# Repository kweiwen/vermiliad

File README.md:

# Vermiliad - An open-source hardware solution for building digital modular synthesizers
* DSP, Pure Data, and Controlled Voltage in a single pcb!
* 數位訊號處理、Pure Data、控制電壓融合在在一塊小小的PCB！

## DEMO1:
* 第一段影片展示了Talk-Through功能。首先使用 `aplay -l` 命令確認聲卡的輸入/輸出配置，隨後透過 `mplayer` 命令播放網絡電台。
* The first clip demonstrates the Talk-Through feature. It begins by using the `aplay -l` command to confirm the input/output configuration of the sound card, followed by playing an internet radio station using the `mplayer` command.
* 第二段影片展現了Pitch Shifting的Echo效果。該功能是透過Pure Data實現的，音源輸入來自於Benjolin。
* The second clip showcases the Echo effect of Pitch Shifting. This function is implemented through Pure Data, with the audio input sourced from Benjolin.
* 第三段影片的設置與第二段相同，但在效果器的參數上進行了調整。
* The setup in the third clip is the same as in the second, but with adjustments made to the parameters of the effects processor.
<video src="https://github-production-user-asset-6210df.s3.amazonaws.com/15021145/285418308-6633f0b2-d7b3-4ce2-ba0a-d69b2f7387a2.mp4" width="320" controls></video>

## DEMO2:
* 最後一段影片展示了基於Feedback Delay Network的Granular Delay，這同樣是透過Pure Data實現的，音源輸入來自於Benjolin。
* This final video demonstrates the Granular Delay based on Feedback Delay Networks, also implemented through Pure Data, with the audio input sourced from Benjolin.
<video src="https://github-production-user-asset-6210df.s3.amazonaws.com/15021145/285418398-cd53d4ac-97a0-486a-81fa-60b1c6fd6b72.mp4" width="320" controls></video>

## PCB Layout:

* Top Of Adapter

* Bottom Of Adapter

* Top Of Motherboard

* Bottom Of Motherboard

## Introduction:

This article introduces the master's thesis titled "Building an Open Source Modular Synthesizer Based on the Integration of Raspberry Pi, Python and Pure Data." initiated in late 2015. During my military service in Madou, Tainan, I continuously worked on and developed this project, efficiently adjusting and upgrading various hardware and software components. This module is designed for Real-Time DSP, allowing users to customize modular synthesizer functions on Pure Data. I also implemented Miller Puckette's Feedback Delay Network Reverb on Pure Data, receiving positive feedback. The project is ultimately managed as an open-source initiative, aiming to contribute more to the open-source community and synthesizer enthusiasts.

In terms of software, I found no better method than the UDP interface for transmitting data to Pure Data. I used MCP3008 to receive external control voltage parameters, then transmitted them to the UDP network via Python for Pure Data to read. However, Python's looped data transmission consumed significant memory. Even attempts using Linux Bash loops were unsatisfactory, as a 0.5-millisecond transmission frequency consumed 25% of the CPU and 18% of the memory. Python scripts were affected by Raspberry Pi and other unstable factors, leading to external control delays. Given that Python is an interpreted language, despite methods to improve performance, switching languages proved to be a better option.

Ultimately, I replaced Python with C++ as the interface for communication between MCP3008 and Raspberry Pi. This led to significant improvements: the sampling speed could reach 0.1 milliseconds or even faster, with about 3% memory usage and approximately 5% CPU occupancy. This change enhanced the operation's smoothness and provided more resources for processing audio inside Pure Data.

In hardware, I used the I2S audio transmission interface instead of the previous USB Audio, choosing the WM8731 chip, widely used by many module manufacturers. After upgrading the Linux kernel to 4.4, the I2S driver module was built into the kernel, relieving developers from the hassle of cross-compiling and significantly improving sound quality. The external control voltage circuit was designed with an OP Amp to adjust the voltage range to meet MCP3008's requirements. Major changes were made to the external output of the sound source, mixing the original signal with the Codec output, and using Vactrol to control the dry/wet signal ratio, replacing many DSP-type effects in digital loop control.

The board layout was divided into two parts: the Adapter responsible for Audio I/O and Analog I/O, and the Motherboard for expansion, such as adjusting the voltage to Eurorack Level, Vactrol Mixing, CV Adjustment, etc.

## Epilogue:

Regarding the development of Pure Data, it is regrettable that the main program is no longer updated. The interface and editor have hardly changed, and updates mainly focus on platform expansion, bug fixes, and adding specific libraries. With the stabilization of new platforms like Raspberry Pi, and BeagleBone and the improvement of various libraries and functions, the frequency of updates to the main program has gradually decreased. The new Deken Plugin will become an important tool for managing and adding libraries.

## License
Code: MIT license.

Hardware: cc-by-sa-3.0

By: Tseng Kweiwen

## 簡介:

本文介紹的碩士論文題目「基於Raspberry Pi、Python和Pure Data構建開源模組化合成器」始於2015年底。在服役於台南麻豆期間，我持續實作與開發，對許多硬體與軟體部分進行高效調整和升級。此模組是為了服務Real-Time DSP，允許使用者在Pure Data上自定義模組合成器功能。我還在Pure Data上實現了Miller Puckette的Feedback Delay Network的Reverb，獲得良好回饋。該項目最終以開源方式管理，旨在為開源社區和合成器愛好者貢獻更多。

在軟體方面，我未找到比UDP介面更合適的方法將數據傳輸到Pure Data。我使用MCP3008接收外部控制電壓參數，再通過Python傳輸至UDP網路供Pure Data讀取。然而，Python循環傳輸資料會大量消耗記憶體。即使嘗試過Linux Bash進行循環，結果仍不理想，0.5毫秒的傳輸頻率會消耗25%的CPU和18%的記憶體。Python腳本受Raspberry Pi和其他不穩定因素影響，導致外部控制延遲。鑑於Python是直譯式語言，儘管有提高效能的方法，更換語言仍是更佳選擇。

最終，我改用C++取代Python作為MCP3008與Raspberry Pi的通訊介面。這帶來顯著改善，取樣速度可達0.1毫秒甚至更快，記憶體使用率約3%，CPU佔用率約5%，使操作更加順暢，並為Pure Data提供更多資源。

在硬體方面，我採用I2S音訊傳輸介面取代舊有的USB Audio，選用WM8731晶片，該晶片已被許多模組製造商廣泛使用。Linux kernel升級至4.4後，驅動模組內建於kernel中，開發者無需煩惱cross-compiling，音質也顯著提升。外部控制電壓迴路設計了OP Amp迴路以調整電壓範圍，符合MCP3008的要求，並對音源外部輸出進行重大改動，原始訊號與Codec輸出訊號混合，使用Vactrol控制乾濕訊號比例，替代了許多DSP類型效果器在數位迴路中的控制。

板子布局被分為兩部分：Adapter負責Audio I/O和Analog I/O，Motherboard則用於擴充，例如調整電壓至Eurorack Level、Vactrol Mixing、CV Adjustment等。

## 後記：
在Pure Data的發展上，遺憾的是主程式已不再更新。操控模式介面幾無變化，更新主要針對平台擴充、臭蟲修復和新增特定Library等。隨著新型平台如Raspberry Pi、BeagleBone的穩定，以及多種Library和功能的完善，主程式的更新逐漸減少。新的Deken Plugin將成為管理和新增Library的重要工具。

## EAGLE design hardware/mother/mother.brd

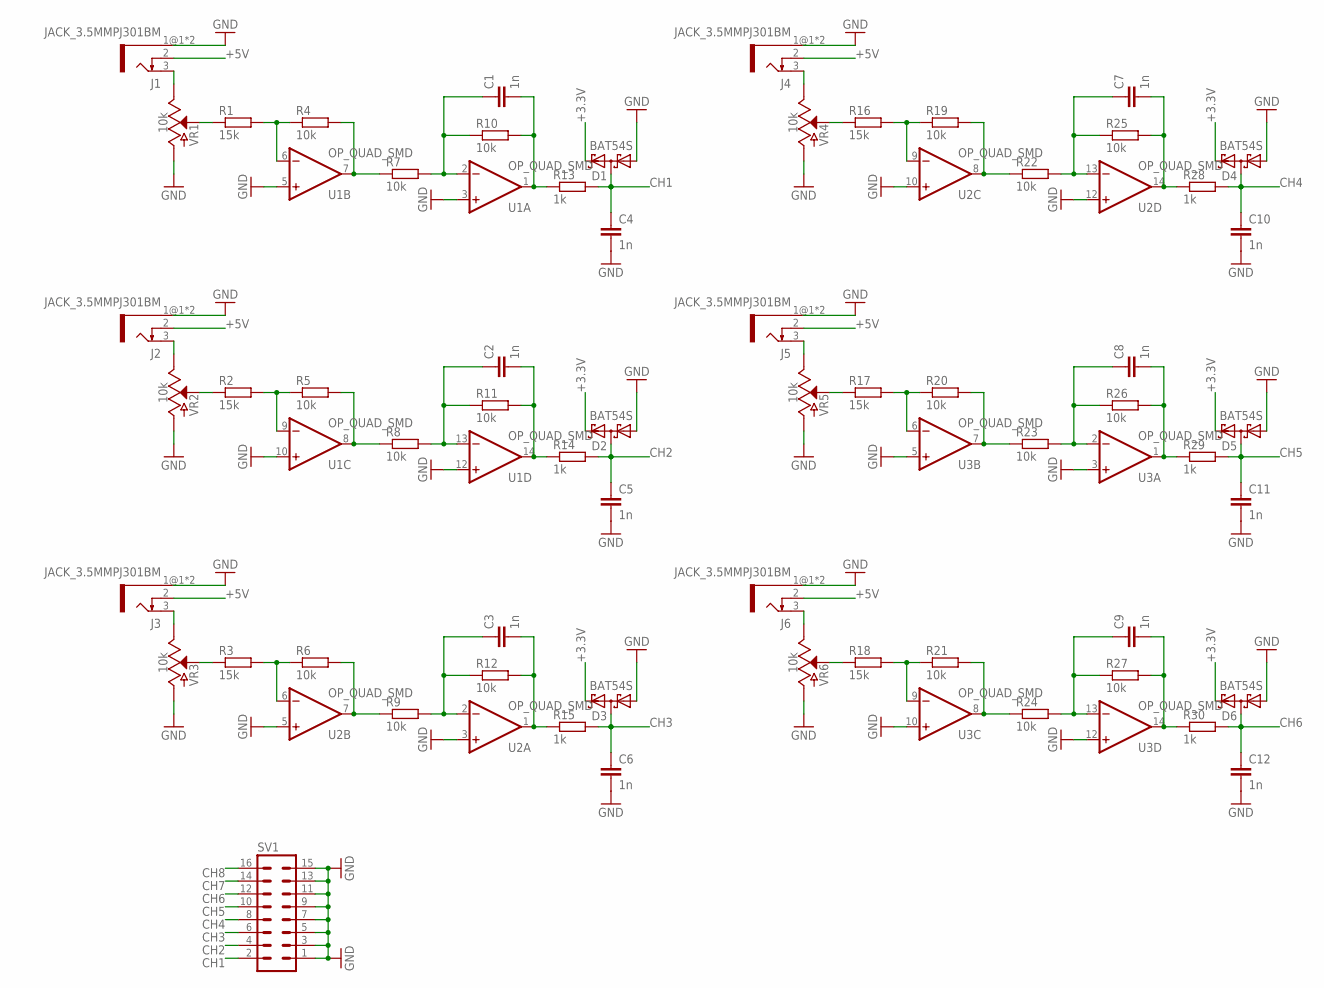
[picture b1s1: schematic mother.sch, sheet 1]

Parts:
C1, C2, C3, C4, C5, C6, C7, C8, C9, C10, C11, C12: 1n; C0603
D1, D2, D3, D4, D5, D6: BAT54S; SOT23
J1, J2, J3, J4, J5, J6: JACK_3.5MMPJ301BM; PJ301BM_JACK
R1, R2, R3, R16, R17, R18: 15k; R0603
R4, R5, R6, R7, R8, R9, R10, R11, R12, R19, R20, R21, R22, R23, R24, R25, R26, R27: 10k; R0603
R13, R14, R15, R28, R29, R30: 1k; R0603
SV1: MA08-2
U1, U2, U3: OP_QUAD_SMD; SO14
VR1, VR2, VR3, VR4, VR5, VR6: 10k; POT-PTH-ALPS-KIT

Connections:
+3.3V: D1.2 (C2), D2.2 (C2), D3.2 (C2), D4.2 (C2), D5.2 (C2), D6.2 (C2); also elsewhere on the board
+5V: J1.2, J2.2, J3.2, J4.2, J5.2, J6.2; also elsewhere on the board
CH1: C4.1, D1.3 (C1A2), R13.2, SV1.2
CH2: C5.1, D2.3 (C1A2), R14.2, SV1.4
CH3: C6.1, D3.3 (C1A2), R15.2, SV1.6
CH4: C10.1, D4.3 (C1A2), R28.2, SV1.8
CH5: C11.1, D5.3 (C1A2), R29.2, SV1.10
CH6: C12.1, D6.3 (C1A2), R30.2, SV1.12
CH7: SV1.14
CH8: SV1.16
GND: C4.2, C5.2, C6.2, C10.2, C11.2, C12.2, D1.1 (A1), D2.1 (A1), D3.1 (A1), D4.1 (A1), D5.1 (A1), D6.1 (A1), J1.1@1 (1), J1.1@2 (1), J2.1@1 (1), J2.1@2 (1), J3.1@1 (1), J3.1@2 (1), J4.1@1 (1), J4.1@2 (1), J5.1@1 (1), J5.1@2 (1), J6.1@1 (1), J6.1@2 (1), SV1.1, SV1.3, SV1.5, SV1.7, SV1.9, SV1.11, SV1.13, SV1.15, U1.3 (+IN), U1.5 (+IN), U1.10 (+IN), U1.12 (+IN), U2.3 (+IN), U2.5 (+IN), U2.10 (+IN), U2.12 (+IN), U3.3 (+IN), U3.5 (+IN), U3.10 (+IN), U3.12 (+IN), VR1.P$1 (A), VR2.P$1 (A), VR3.P$1 (A), VR4.P$1 (A), VR5.P$1 (A), VR6.P$1 (A); also elsewhere on the board
unnamed: R2.1, VR2.P$2 (S)
unnamed: J2.3, VR2.P$3 (E)
unnamed: R1.2, R4.1, U1.6 (-IN)
unnamed: R4.2, R7.1, U1.7 (OUT)
unnamed: C1.1, R7.2, R10.1, U1.2 (-IN)
unnamed: C1.2, R10.2, R13.1, U1.1 (OUT)
unnamed: R1.1, VR1.P$2 (S)
unnamed: R2.2, R5.1, U1.9 (-IN)
unnamed: R5.2, R8.1, U1.8 (OUT)
unnamed: J1.3, VR1.P$3 (E)
unnamed: C2.1, R8.2, R11.1, U1.13 (-IN)
unnamed: C2.2, R11.2, R14.1, U1.14 (OUT)
unnamed: R16.2, R19.1, U2.9 (-IN)
unnamed: R19.2, R22.1, U2.8 (OUT)
unnamed: C7.1, R22.2, R25.1, U2.13 (-IN)
unnamed: C7.2, R25.2, R28.1, U2.14 (OUT)
unnamed: R16.1, VR4.P$2 (S)
unnamed: J4.3, VR4.P$3 (E)
unnamed: R3.2, R6.1, U2.6 (-IN)
unnamed: R6.2, R9.1, U2.7 (OUT)
unnamed: C3.1, R9.2, R12.1, U2.2 (-IN)
unnamed: C3.2, R12.2, R15.1, U2.1 (OUT)
unnamed: R3.1, VR3.P$2 (S)
unnamed: J3.3, VR3.P$3 (E)
unnamed: R18.2, R21.1, U3.9 (-IN)
unnamed: R21.2, R24.1, U3.8 (OUT)
unnamed: C9.1, R24.2, R27.1, U3.13 (-IN)
unnamed: C9.2, R27.2, R30.1, U3.14 (OUT)
unnamed: R18.1, VR6.P$2 (S)
unnamed: J6.3, VR6.P$3 (E)
unnamed: R17.2, R20.1, U3.6 (-IN)
unnamed: R20.2, R23.1, U3.7 (OUT)
unnamed: C8.1, R23.2, R26.1, U3.2 (-IN)
unnamed: C8.2, R26.2, R29.1, U3.1 (OUT)
unnamed: R17.1, VR5.P$2 (S)
unnamed: J5.3, VR5.P$3 (E)

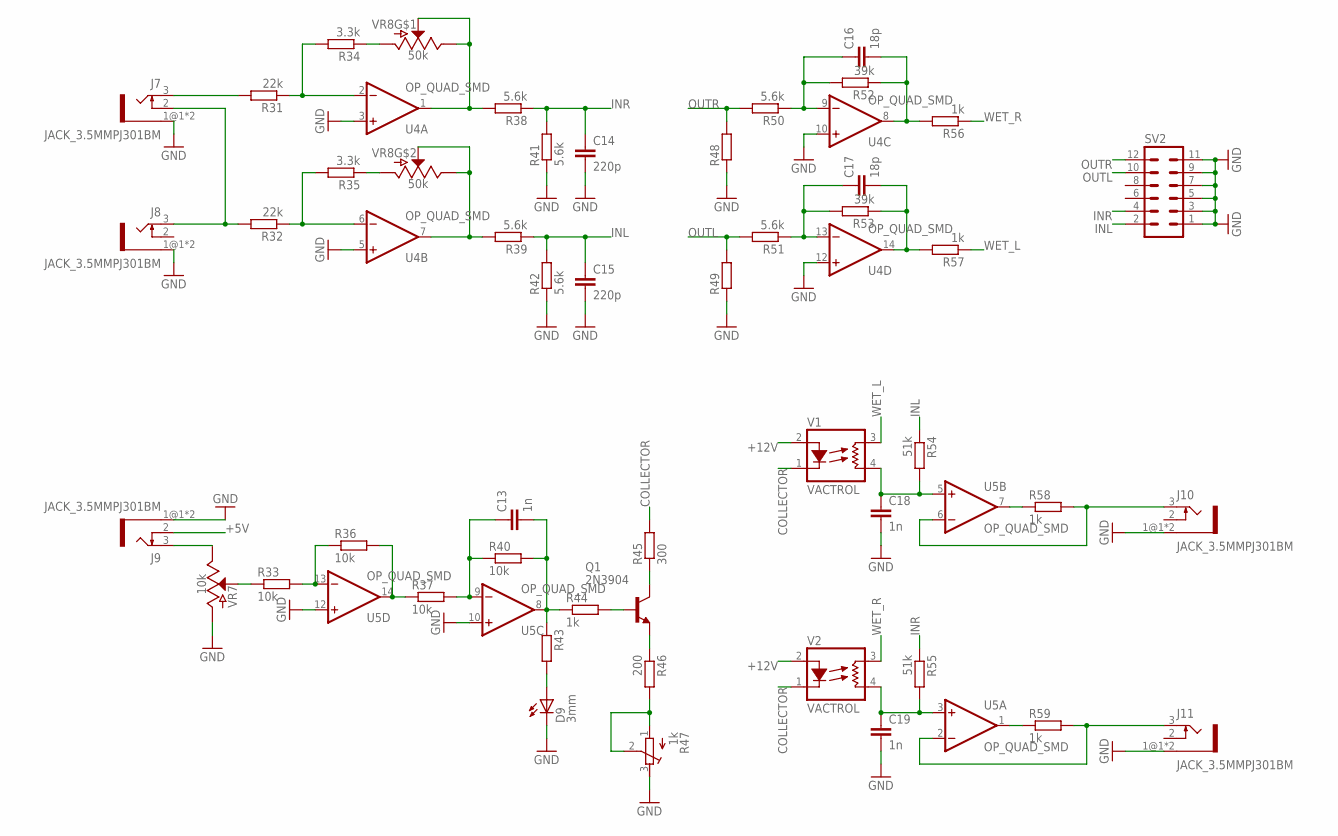
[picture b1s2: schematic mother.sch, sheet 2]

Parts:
C13, C18, C19: 1n; C0603
C14, C15: 220p; C0603
C16, C17: 18p; C0603
D9: 3mm; LED3MM
J7, J8, J9, J10, J11: JACK_3.5MMPJ301BM; PJ301BM_JACK
Q1: 2N3904; TO92
R31, R32: 22k; R0603
R33, R36, R37, R40: 10k; R0603
R34, R35: 3.3k; R0603
R38, R39, R41, R42, R50, R51: 5.6k; R0603
R43: RESISTOR10MM; 1/4W_RESISTOR
R44, R56, R57, R58, R59: 1k; R0603
R45: 300; 1/4W_RESISTOR
R46: 200; R0603
R47: 1k; RTRIM64W
R48, R49: RR0603; R0603
R52, R53: 39k; R0603
R54, R55: 51k; R0603
SV2: MA06-2
U4, U5: OP_QUAD_SMD; SO14
V1, V2: VACTROL; VACTROL_4PIN_VTL5C
VR7: 10k; POT-PTH-ALPS-KIT
VR8: 50k; POT-DUAL-PTH-PANASONIC-VERT-KIT

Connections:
+5V: J9.2; also elsewhere on the board
+12V: V1.2 (LED+), V2.2 (LED+); also elsewhere on the board
COLLECTOR: R45.2, V1.1 (LED-), V2.1 (LED-)
GND: C14.2, C15.2, C18.2, C19.2, D9.K (C), J7.1@1 (1), J7.1@2 (1), J8.1@1 (1), J8.1@2 (1), J9.1@1 (1), J9.1@2 (1), J10.1@1 (1), J10.1@2 (1), J11.1@1 (1), J11.1@2 (1), R41.1, R42.1, R47.3 (A), R48.1, R49.1, SV2.1, SV2.3, SV2.5, SV2.7, SV2.9, SV2.11, U4.3 (+IN), U4.5 (+IN), U4.10 (+IN), U4.12 (+IN), U5.10 (+IN), U5.12 (+IN), VR7.P$1 (A); also elsewhere on the board
INL: C15.1, R39.1, R42.2, R54.1, SV2.2
INR: C14.1, R38.1, R41.2, R55.1, SV2.4
unnamed: J9.3, VR7.P$3 (E)
unnamed: C13.2, R40.2, R43.1, R44.1, U5.8 (OUT)
unnamed: R33.1, VR7.P$2 (S)
unnamed: R33.2, R36.1, U5.13 (-IN)
unnamed: R36.2, R37.1, U5.14 (OUT)
unnamed: C13.1, R37.2, R40.1, U5.9 (-IN)
unnamed: D9.A, R43.2
unnamed: J10.3, R58.2, U5.6 (-IN)
unnamed: R58.1, U5.7 (OUT)
unnamed: C18.1, R54.2, U5.5 (+IN), V1.4 (RES2)
unnamed: Q1.3 (E), R46.1
unnamed: R46.2, R47.1 (E), R47.2 (S)
unnamed: Q1.1 (C), R45.1
unnamed: R34.1, VR8.A1 (A)
unnamed: Q1.2 (B), R44.2
unnamed: J11.3, R59.2, U5.2 (-IN)
unnamed: R59.1, U5.1 (OUT)
unnamed: C19.1, R55.2, U5.3 (+IN), V2.4 (RES2)
unnamed: R35.1, VR8.B1 (A)
unnamed: J7.2, J8.3, R32.2
unnamed: J7.3, R31.2
unnamed: C17.1, R51.1, R53.2, U4.13 (-IN)
unnamed: C17.2, R53.1, R57.2, U4.14 (OUT)
unnamed: C16.1, R50.1, R52.2, U4.9 (-IN)
unnamed: C16.2, R52.1, R56.2, U4.8 (OUT)
unnamed: R38.2, U4.1 (OUT), VR8.A2 (S), VR8.A3 (E)
unnamed: R39.2, U4.7 (OUT), VR8.B2 (S), VR8.B3 (E)
unnamed: R31.1, R34.2, U4.2 (-IN)
unnamed: R32.1, R35.2, U4.6 (-IN)
OUTL: R49.2, R51.2, SV2.10
OUTR: R48.2, R50.2, SV2.12
WET_L: R57.1, V1.3 (RES1)
WET_R: R56.1, V2.3 (RES1)

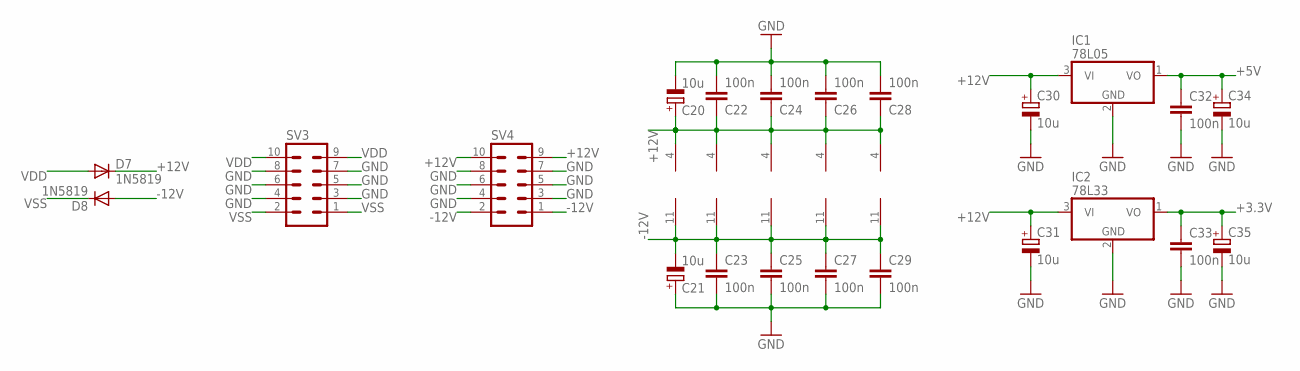
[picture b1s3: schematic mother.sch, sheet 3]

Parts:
C20, C21, C30, C31, C34, C35: 10u; E2,5-6
C22, C23, C24, C25, C26, C27, C28, C29, C32, C33: 100n; C5B3.5
D7, D8: 1N5819; SOD-123_MINI-SMA
IC1: 78L05; TO92
IC2: 78L33; TO92
SV3, SV4: MA05-2
U1, U2, U3, U4, U5: OP_QUAD_SMD; SO14

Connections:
+3.3V: C33.1, C35.+, IC2.1 (VO); also elsewhere on the board
+5V: C32.1, C34.+, IC1.1 (VO); also elsewhere on the board
+12V: C20.+, C22.1, C24.1, C26.1, C28.1, C30.+, C31.+, D7.C, IC1.3 (VI), IC2.3 (VI), SV4.9, SV4.10, U1.4 (V+), U2.4 (V+), U3.4 (V+), U4.4 (V+), U5.4 (V+); also elsewhere on the board
-12V: C21.-, C23.1, C25.1, C27.1, C29.1, D8.A, SV4.1, SV4.2, U1.11 (V-), U2.11 (V-), U3.11 (V-), U4.11 (V-), U5.11 (V-)
GND: C20.-, C21.+, C22.2, C23.2, C24.2, C25.2, C26.2, C27.2, C28.2, C29.2, C30.-, C31.-, C32.2, C33.2, C34.-, C35.-, IC1.2 (GND), IC2.2 (GND), SV3.3, SV3.4, SV3.5, SV3.6, SV3.7, SV3.8, SV4.3, SV4.4, SV4.5, SV4.6, SV4.7, SV4.8; also elsewhere on the board
VDD: D7.A, SV3.9, SV3.10
VSS: D8.C, SV3.1, SV3.2

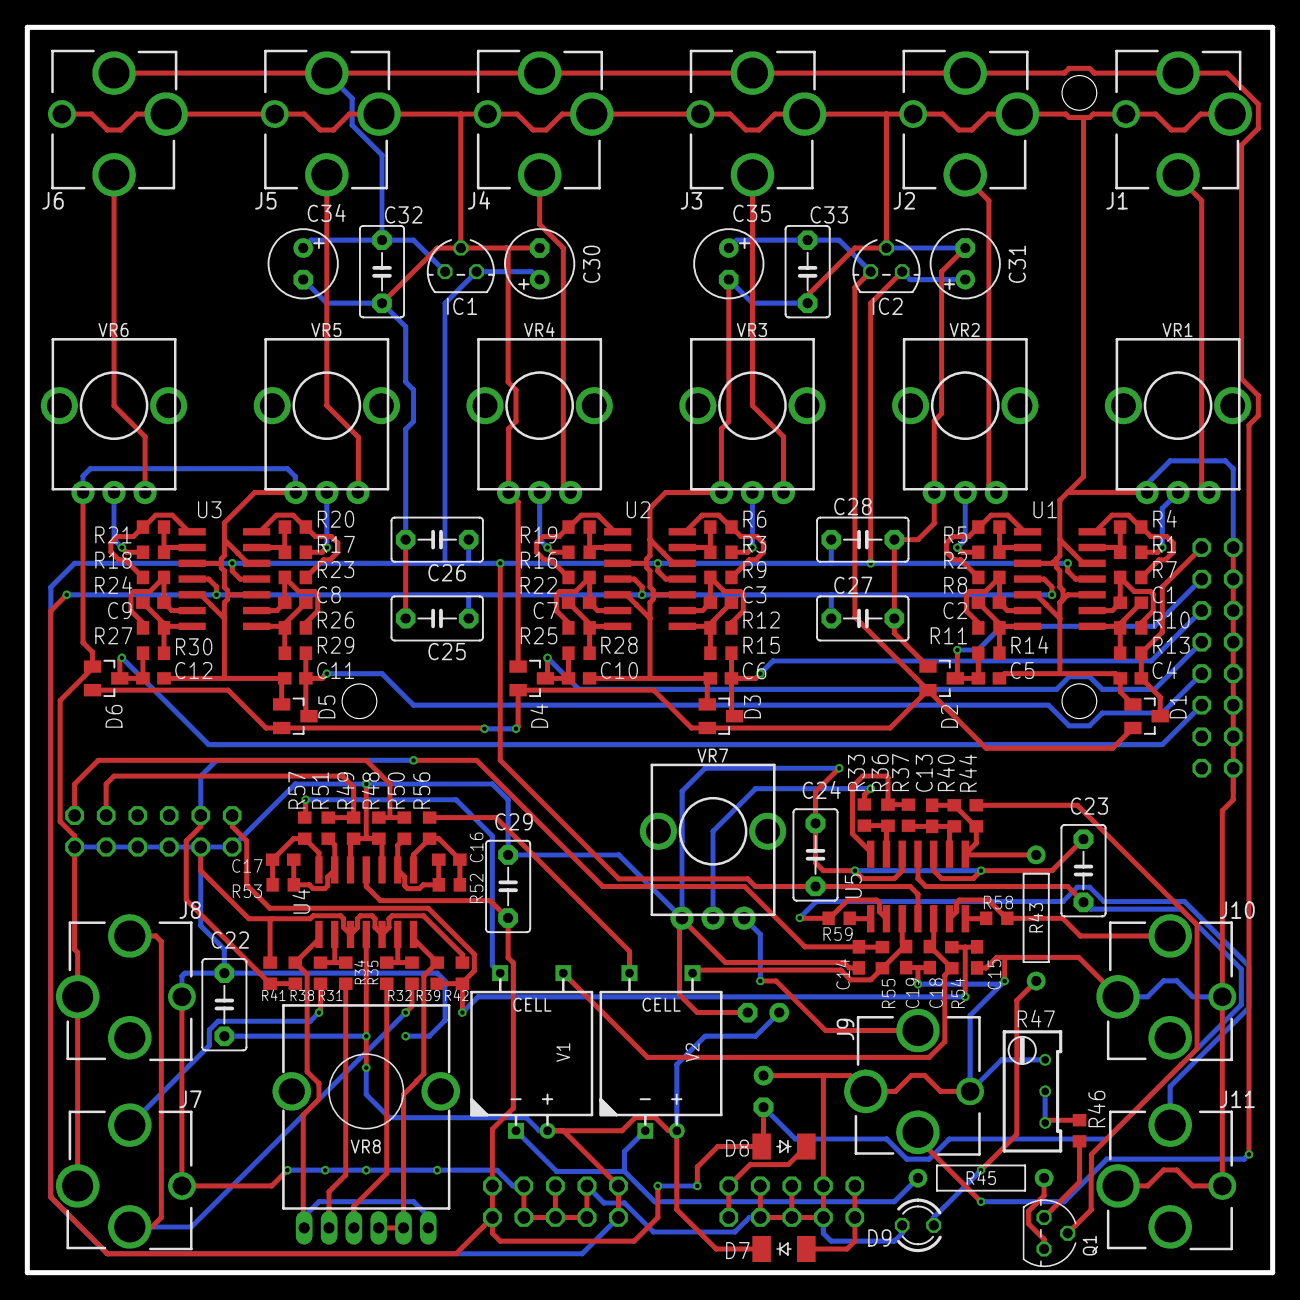
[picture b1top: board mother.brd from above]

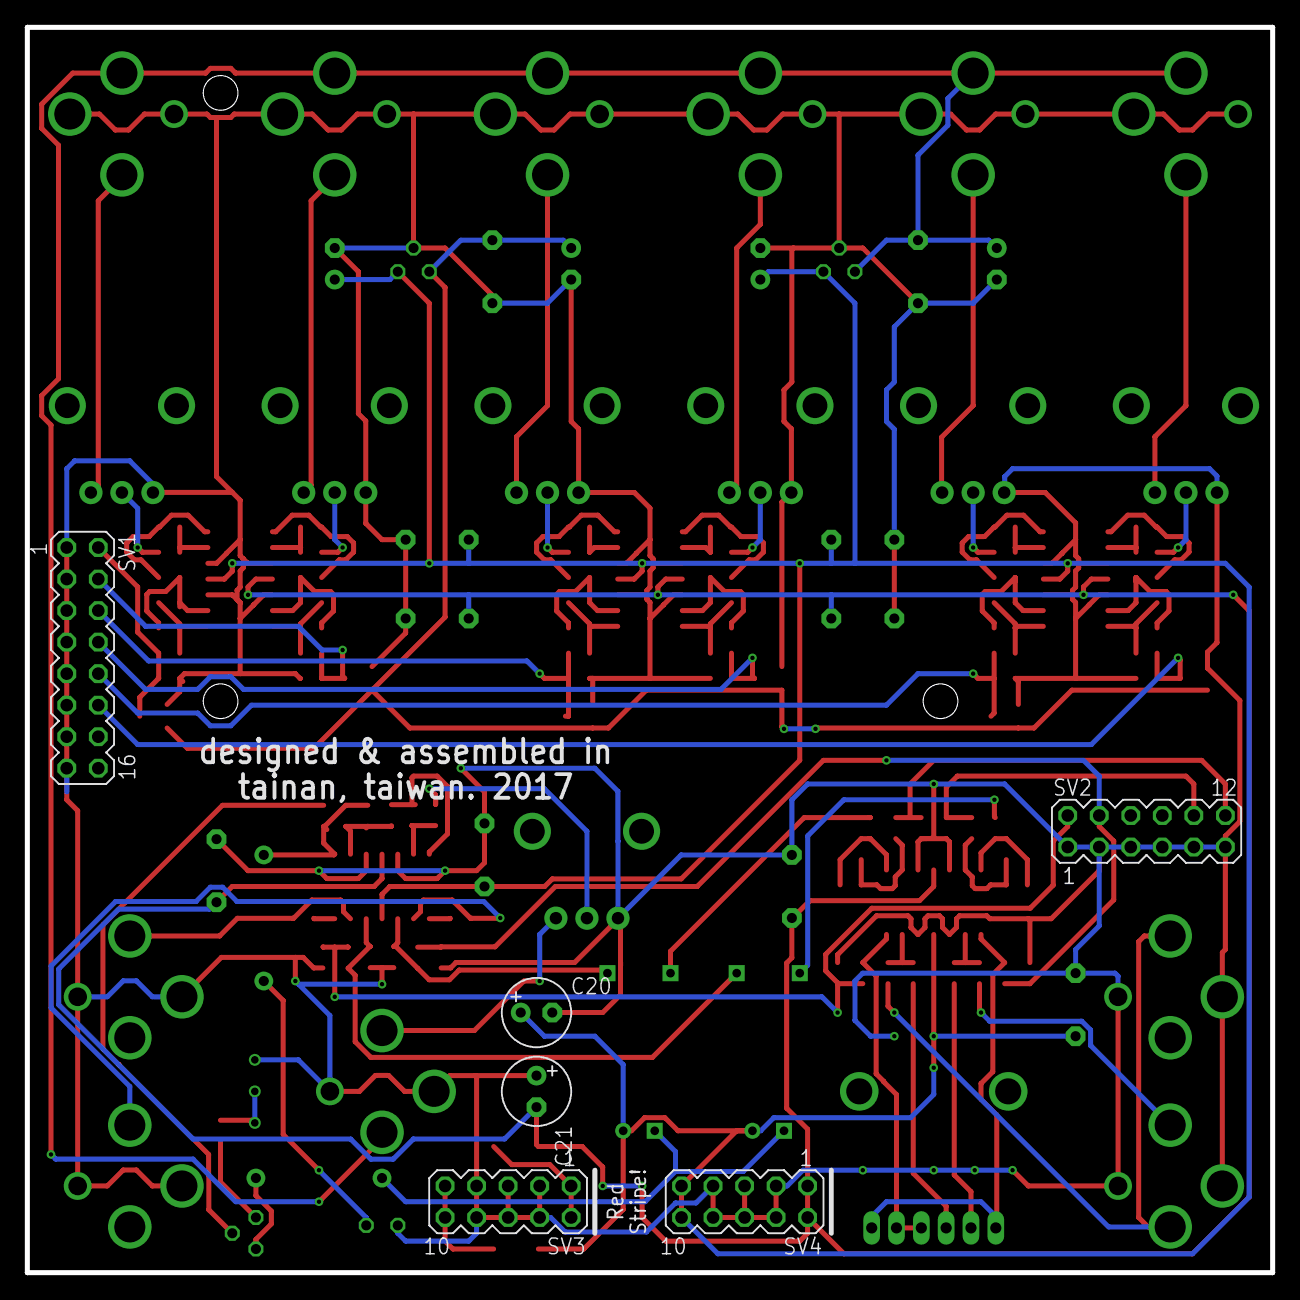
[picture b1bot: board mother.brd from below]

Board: 2 copper layers, 100.3 x 100.3 mm, 136 parts (6 on the bottom side), 85 nets.

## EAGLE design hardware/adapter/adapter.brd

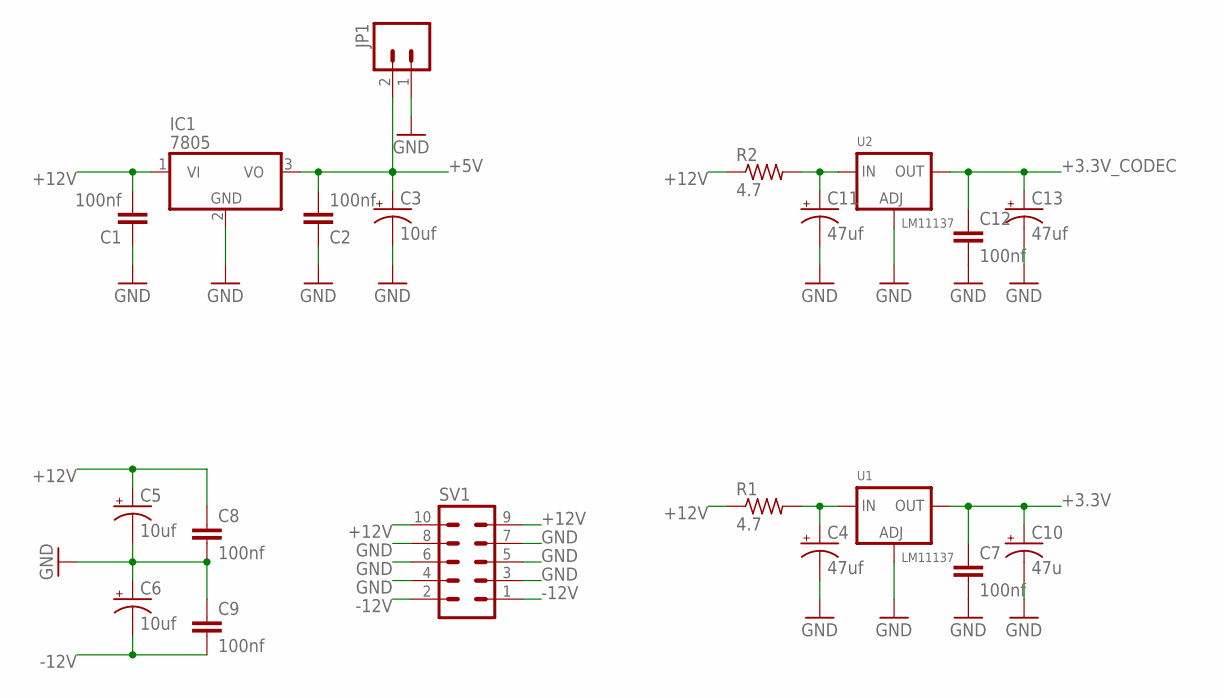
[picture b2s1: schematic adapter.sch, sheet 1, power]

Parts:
C1, C2, C7, C8, C9, C12: 100nf; C0603
C3, C5, C6: 10uf; PANASONIC_C
C4, C11, C13: 47uf; PANASONIC_D
C10: 47u; PANASONIC_D
IC1: 7805; TO220V
JP1: M02_HEADERPOLAR; MOLEX-1X2
R1, R2: 4.7; R1206
SV1: MA05-2
U1: LM11137; TO252
U2: LM11137; SOT223-R

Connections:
+3.3V: C7.1, C10.+, U1.3 (OUT); also elsewhere on the board
+3.3V_CODEC: C12.1, C13.+, U2.2 (OUT); also elsewhere on the board
+5V: C2.2, C3.+, IC1.3 (VO), JP1.2; also elsewhere on the board
+12V: C1.2, C5.+, C8.1, IC1.1 (VI), R1.1, R2.1, SV1.9, SV1.10
-12V: C6.-, C9.2, SV1.1, SV1.2
GND: C1.1, C2.1, C3.-, C4.-, C5.-, C6.+, C7.2, C8.2, C9.1, C10.-, C11.-, C12.2, C13.-, IC1.2 (GND), JP1.1, SV1.3, SV1.4, SV1.5, SV1.6, SV1.7, SV1.8, U1.1 (ADJ), U2.1 (ADJ); also elsewhere on the board
unnamed: C11.+, R2.2, U2.3 (IN)
unnamed: C4.+, R1.2, U1.2 (IN)

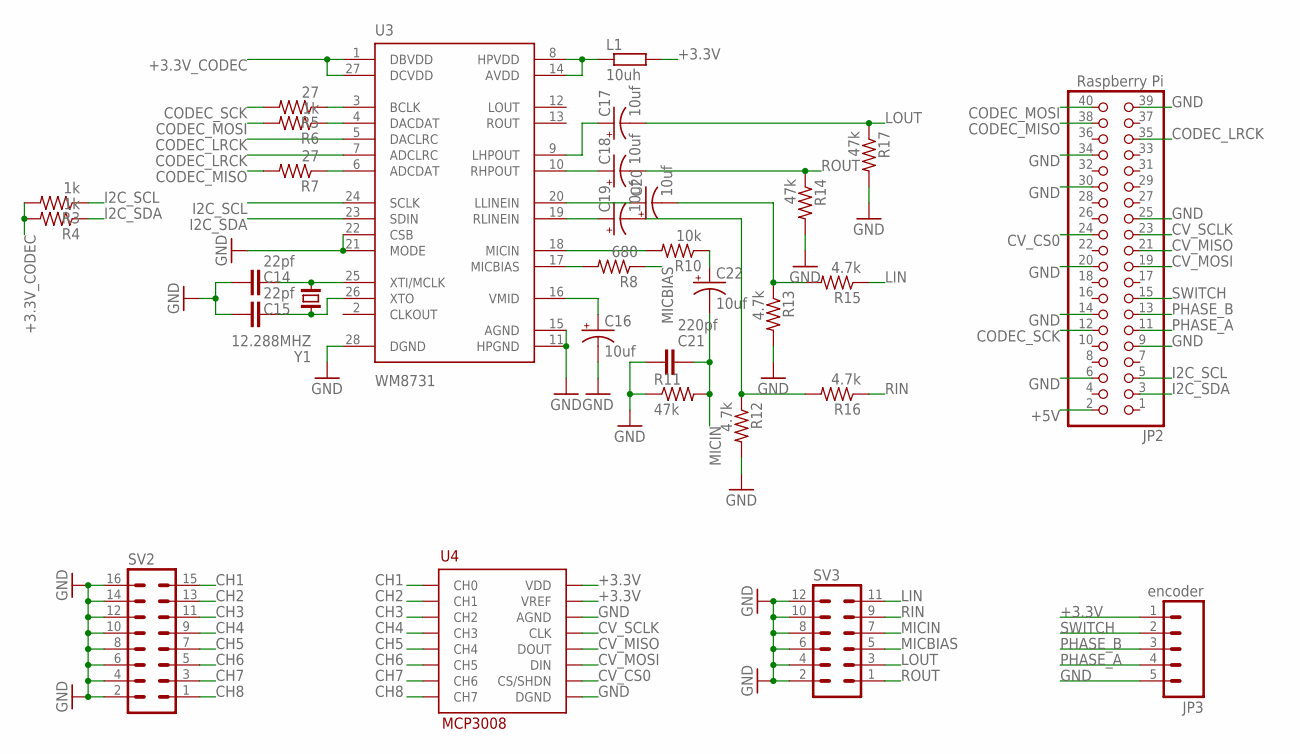
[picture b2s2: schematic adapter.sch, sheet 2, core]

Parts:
C14, C15: 22pf; C0603
C16, C17, C18, C19, C20, C22: 10uf; PANASONIC_C
C21: 220pf; C0603
JP2: Raspberry Pi; 2X20
JP3: encoder; 1X05
L1: 10uh; 1/4W_RESISTOR
R3, R4, R6: 1k; R0603
R5, R7: 27; R0603
R8: 680; R0603
R10: 10k; R0603
R11, R14, R17: 47k; R0603
R12, R13, R15, R16: 4.7k; R0603
SV2: MA08-2
SV3: MA06-2
U3: WM8731; SSOP28
U4: MCP3008; SOIC16
Y1: 12.288MHZ; HC49UP

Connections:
+3.3V: JP3.1, L1.2, U4.15 (VREF), U4.16 (VDD); also elsewhere on the board
+3.3V_CODEC: R3.2, R4.2, U3.1 (DBVDD), U3.27 (DCVDD); also elsewhere on the board
+5V: JP2.2; also elsewhere on the board
CH1: SV2.15, U4.1 (CH0)
CH2: SV2.13, U4.2 (CH1)
CH3: SV2.11, U4.3 (CH2)
CH4: SV2.9, U4.4 (CH3)
CH5: SV2.7, U4.5 (CH4)
CH6: SV2.5, U4.6 (CH5)
CH7: SV2.3, U4.7 (CH6)
CH8: SV2.1, U4.8 (CH7)
CODEC_LRCK: JP2.35, U3.5 (DACLRC), U3.7 (ADCLRC)
CODEC_MISO: JP2.38, R7.2
CODEC_MOSI: JP2.40, R6.2
CODEC_SCK: JP2.12, R5.2
CV_CS0: JP2.24, U4.10 (CS/SHDN)
CV_MISO: JP2.21, U4.12 (DOUT)
CV_MOSI: JP2.19, U4.11 (DIN)
CV_SCLK: JP2.23, U4.13 (CLK)
GND: C14.2, C15.2, C16.-, C21.1, JP2.6, JP2.9, JP2.14, JP2.20, JP2.25, JP2.30, JP2.34, JP2.39, JP3.5, R11.1, R12.2, R13.2, R14.2, R17.2, SV2.2, SV2.4, SV2.6, SV2.8, SV2.10, SV2.12, SV2.14, SV2.16, SV3.2, SV3.4, SV3.6, SV3.8, SV3.10, SV3.12, U3.11 (HPGND), U3.15 (AGND), U3.21 (MODE), U3.22 (CSB), U3.28 (DGND), U4.9 (DGND), U4.14 (AGND); also elsewhere on the board
I2C_SCL: JP2.5, R3.1, U3.24 (SCLK)
I2C_SDA: JP2.3, R4.1, U3.23 (SDIN)
LIN: R15.1, SV3.11
LOUT: C17.-, R17.1, SV3.3
MICBIAS: R8.1, SV3.5
MICIN: C21.2, C22.-, R11.2, SV3.7
unnamed: R5.1, U3.3 (BCLK)
unnamed: R6.1, U3.4 (DACDAT)
unnamed: R7.1, U3.6 (ADCDAT)
unnamed: C19.-, R12.1, R16.2
unnamed: C20.+, U3.20 (LLINEIN)
unnamed: C19.+, U3.19 (RLINEIN)
unnamed: C20.-, R13.1, R15.2
unnamed: R8.2, U3.17 (MICBIAS)
unnamed: R10.2, U3.18 (MICIN)
unnamed: C22.+, R10.1
unnamed: L1.1, U3.8 (HPVDD), U3.14 (AVDD)
unnamed: C17.+, U3.9 (LHPOUT)
unnamed: C16.+, U3.16 (VMID)
unnamed: C14.1, U3.25 (XTI/MCLK), Y1.2
unnamed: C15.1, U3.26 (XTO), Y1.1
unnamed: C18.+, U3.10 (RHPOUT)
PHASE_A: JP2.11, JP3.4
PHASE_B: JP2.13, JP3.3
RIN: R16.1, SV3.9
ROUT: C18.-, R14.1, SV3.1
SWITCH: JP2.15, JP3.2

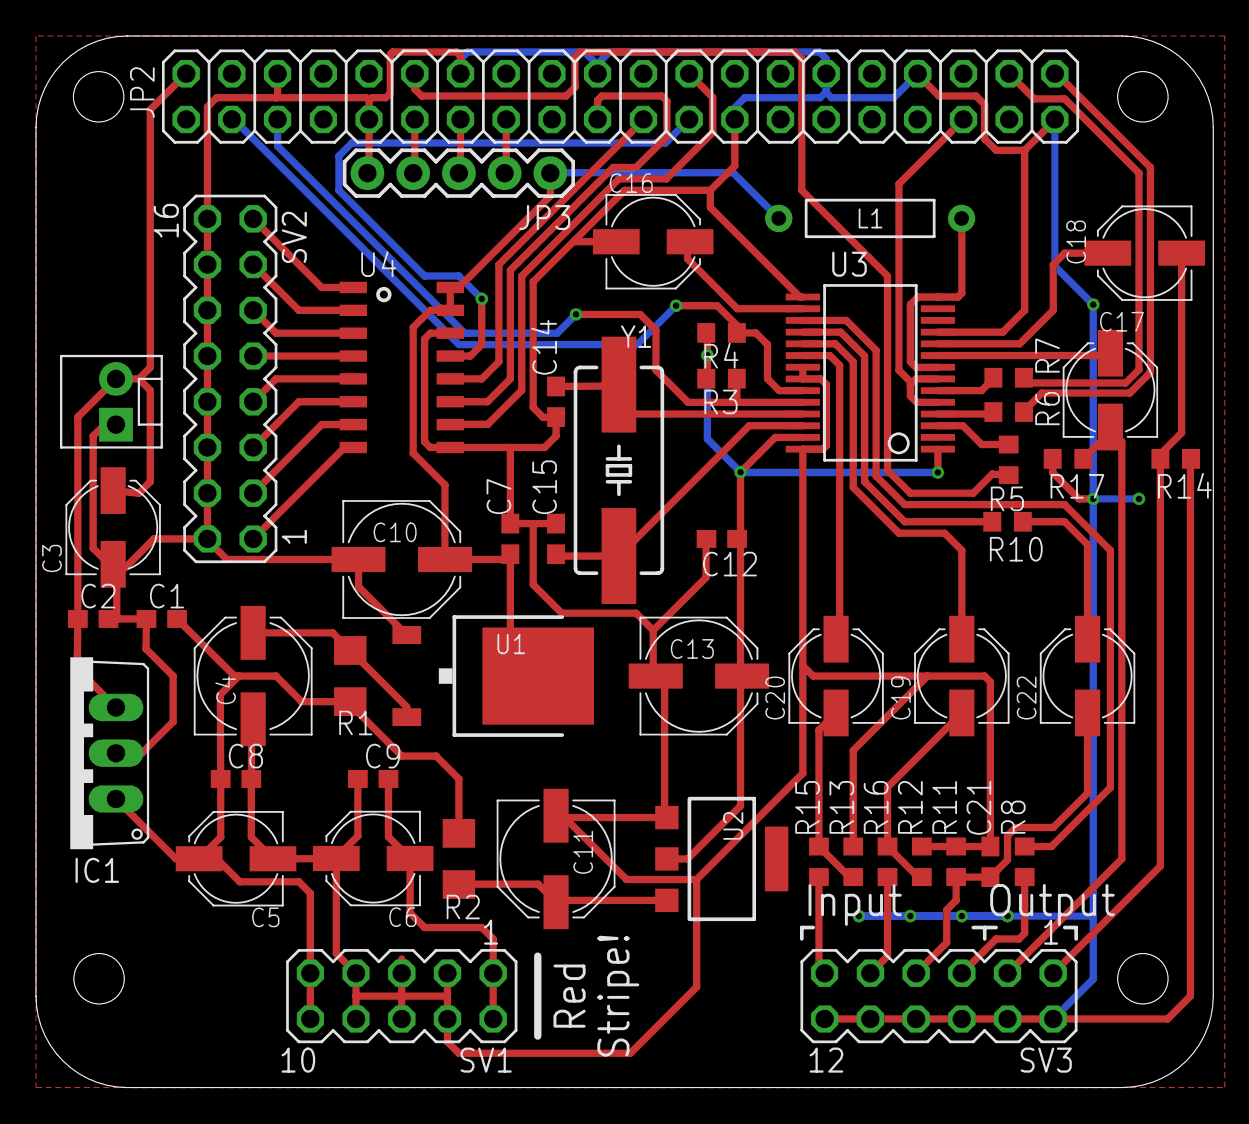
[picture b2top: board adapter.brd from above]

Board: 2 copper layers, 65.4 x 58.4 mm, 51 parts (0 on the bottom side), 51 nets.

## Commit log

2017-07-03 First Update
2017-07-04 Feedback delay network fixed
2017-07-04 Adjust layout
2017-07-19 SPDT ON-ON
2017-07-20 Revert "Update"
    This reverts commit 1fa1ac1b62750ae01fc9ebf9e2e8e41934c85bca, reversing
    changes made to 5a165f026fc5e219df6fc06eabf06e676fb6696f.
2020-06-25 vst-sdk first commit
2020-06-25 xcovde proj
2020-06-25 gain implementation in delay vst example
2020-06-25 update mix, circular buffer to delay plugin :)
2020-06-25 add linear one pole param smooth class
2020-12-05 update the tree list
2020-12-14 update git ignore
2020-12-14 first commit reverb
2020-12-15 test
2020-12-19 update the destructor
2021-01-05 no message
2021-01-06 remove unused part

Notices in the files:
parts and their libraries:
pimoroni: Licensing: CC v3.0 Share-Alike You are welcome to use this library for commercial purposes.
microbuilder: This work is placed in the public domain, and may be freely used for commercial and non-commercial work with the following conditions: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
